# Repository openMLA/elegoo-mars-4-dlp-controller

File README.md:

# Raspberry Pi hat for Elegoo Mars 4 DLP board 

A hat for the raspberry pi that allows a resin 3D printer's **UV light** projector to be controlled. Note that this is (in direct form) only suitable for the projector in the Mars 4 DLP. If you have other boards check out the repository for the [Anycubic Photon Ultra](https://github.com/openMLA/photon-ultra-controller), or get in touch for modifications needed. 

The designs in this repository then allow you to project arbitrary **2560x1440** images with UV light on a surface. The native projected pixel size is **50μm**, making PCB fabrication an interesting application. All you would need is a bit of glue code to convert the Gerber files to a rasterised image and then you could easily use the existing 3D printer frame to expose PCB boards. Since you have all the files and access to the code, you can easily tune it to whatever production needs you have.

The UV projector of the Elegoo Mars 4 DLP is [developed and produced by Anhua (D63ZS50B)](https://www.anhuaoe.com/en/industriause/info.aspx?itemid=2694), and seems to be this variety. Under the hood it uses the Texas Instruments DLP300s or DLP301s digital micromirror array.

> [!NOTE]  
> While PCB fabrication is the most straightforward application for this board, this is actually developed as part of an effort towards an open hardware photolithography system. Check out the [openMLA organisation](https://github.com/openMLA/) for more info.

> If you have a projector using the DLPC1438 that uses the parallel video interface (rather than SPI) then you can check out the [PCB design and implementation for the Anycubic Photon Ultra](https://github.com/openMLA/photon-ultra-controller) projector.

### 🚀 At a glance

Running an SPI clock of ~125MHz it takes:

* ~0.75s to send a full 1440p image to the projector
* ~0.18s to send a 720p image to projector

Arbitrary sections of the display can be updated for even shorter transfer times. Note the maximum framerate (below) and that due to technical reasons the smallest image block that can be sent (in terms of transfer size) is 128x2 pixels. 

The image is stored in a buffer in the FPGA, so you can incrementally build or update an image, if that saves you time or makes your life easier.

The max achievable framerate seems to be about 10Hz (as there are some artefacts if you update faster). This is not a hard limit I suspect, and it may be possible to get closer to the display signal framerate of 60Hz.

### 💡 Sourcing the Projector

The easiest and cheapest way to source the projector is to buy a Elegoo Mars 4 DLP. At the time of writing (2024-02-02) the resin printer can be purchased in the EU for 275 euro (discounted).

Alternatively, the projector can be purchased directly from Anhua; but there may be small differences in the heatsink, LED source and other items. Also expect to pay a premium due to shipping, broker cost etc.

### 📃 Project BOM

The total costs for the project consists of 3 parts:

| Expense Description        | Cost  |
| -------------------------- | ----- |
| Elegoo Mars 4 DLP          | 274   |
| Electronics/PCB            | 52.38 |
| Enclosure/3D printed parts | -     |

_The PCB costs are further broken down [in the BOM in the PCB directory](./PCB/README.md)_

### 🎁 3D printable enclosure

A basic 3D printable enclosure is available in the enclosure directory. 

### 🛠 Disassembly 

Disassembly of the printer is not difficult, but I suggest you take a look at the points below before starting.

1. Make sure the projector is working properly by running the display test functions on the original elegoo board.
2. Raise the Z axis all the way to the top. It will only get in the way otherwise. You can also completely remove it later.
3. Remove the front panel. You will need allen keys and philips head screwdrivers. Carefully disconnect the display ribbon cable. Now you should be able to reach the connectors on the mainboard.
4. Disconnect all the connectors on the elegoo mainboard (the one not on top of the projector unit).
5. Undo the screws holding the bottom section of the printer enclosure in place. Now you carefully try to slide it forward and out of the way of the projector. This can be a bit tricky.
6. [optional] If don't want to use the projector in the original elegoo enclosure, you can remove it from the case with the 4 philips head screws holding it in place.

### 🛠 Assembly 

Assembly of the board is pretty straightforward. For completeness, here are the steps you will need to take.

1. Solder headers onto raspberry pi zero.
2. Assembly the custom PCB
3. Flash Raspberry Pi OS Lite onto an micro SD card. You can use [the raspberry pi imager](https://www.raspberrypi.com/software/) for this. Make sure to configure the wireless connection and ssh access in this step.
4. Attach the custom PCB to the raspberry pi zero header.
5. Plug in the 2 pico-claps connectors that were connected to the original elegoo mainboard
6. Plug in the original elegoo power supply to the barrel jack on the custom PCB.
7. Follow the more detailed [software setup](software-setup.md) to get the Pi up and running. 
8. [optional] if you want to use the projector inside the original enclosure, you can check out the instructions in [the enclosure directory](./enclosure/README.md)

### ✅ Future plans

2. Polish package with proper debug level logging and maybe proper formatted python documentation.
3. Add CRC16 checks. (low priority)

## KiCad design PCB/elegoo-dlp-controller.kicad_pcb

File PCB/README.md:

# PCB design

To control the DMD with a raspberry pi, we need a very simple board that allows us to plug in the original Anhua board's connectors (Molex Pico-clasp). Check out [the schematic 🗺](elegoo-dlp-controller.pdf) for the quickest overview of all functionality.

To make our life a little easier, you can add an (optional) dc-dc converter that also converts the 12V to 5V and uses that to power the raspberry pi. This means you do not need to apply separate 5V power to the raspberry pi, and that the 12V needed for the Anhua board provided by the Elegoo Mars 4's power supply is enough to power everything.

Finally, the board breaks out some extra pins for adding your own extra custom bits. SPI and I2C connections, as well as some spare GPIO pins. This may be useful if you want to have exposure occur based on some sensor readout, or maybe tie UV exposure to a simple button for batch production where you don't want to send commands over SSH.

> [!IMPORTANT]  
> Not every connection has been verified to work. I suspect they are all fine since its not a very complex board or high frequency signals. At least the minimum set of pins required for data/exposure seem to work fine.

### Bill of materials

The costs below are indicative, as shipping cost and price changes may have occurred since writing this document. Check with KiCAD's schematic to see if it all up to date. All listed values are including taxes (21%).

| Description                | Supplier         | Supplier Part Number | Amount | Total Cost | Comment                                      |
| -------------------------- | ---------------- | -------------------- | ------ | ---------- | -------------------------------------------- |
| PCB manufacturing          | Aisler           |                      | 3      | 14         | MOC 3pcs                                     |
| Raspberry Pi Zero 2        | Mouser           | 358-SC0510           | 1      | 17         |                                              |
| Micro SD Card (32GB)       | Kiwi Electronics | TS32GUSDU1           | 1      | 10         | Whatever kind you want would work            |
| Raspberry pi header        | Kiwi Electronics | KW-2639              | 1      | 2          | or any basic, cheaper header                 |
| Raspberry pi header female | Kiwi Electronics | KW-1650              | 1      | 1.5        |                                              |
| JST SH 4-pin               | Mouser           | 474-PRT-14417        | 1      | 0.67       | Optional, allows i2c through  stemmaQT/QWIIC |
| Molex PicoClasp 12 pin     | Mouser           | 538-501331-1207      | 1      | 1.19       |                                              |
| Molex PicoClasp 8 pin      | Mouser           | 538-501331-0807      | 1      | 0.92       |                                              |
| Cui DC-DC converter        | Mouser           | 490-P78E05-1000      | 1      | 3.45       |                                              |
| Barreljack                 | Mouser           | 490-PJ-002B          | 1      | 0.79       |                                              |
| Schottky Diode             | Mouser           | 771-PMEG1020EJ-T/R   | 1      | 0.29       |                                              |
| 100uF capacitor            | Mouser           | 667-EEE-FN1E101UP    | 1      | 0.57       |                                              |
|                            |                  |                      |        |            |                                              |
| Total                      |                  |                      |        | 52.38      |                                              |

### Miscellaneous

* Board was designed in KiCAD 7.0
* I had the board fabricated at Aisler (Germany), at 14 euros (total) for 3 boards.

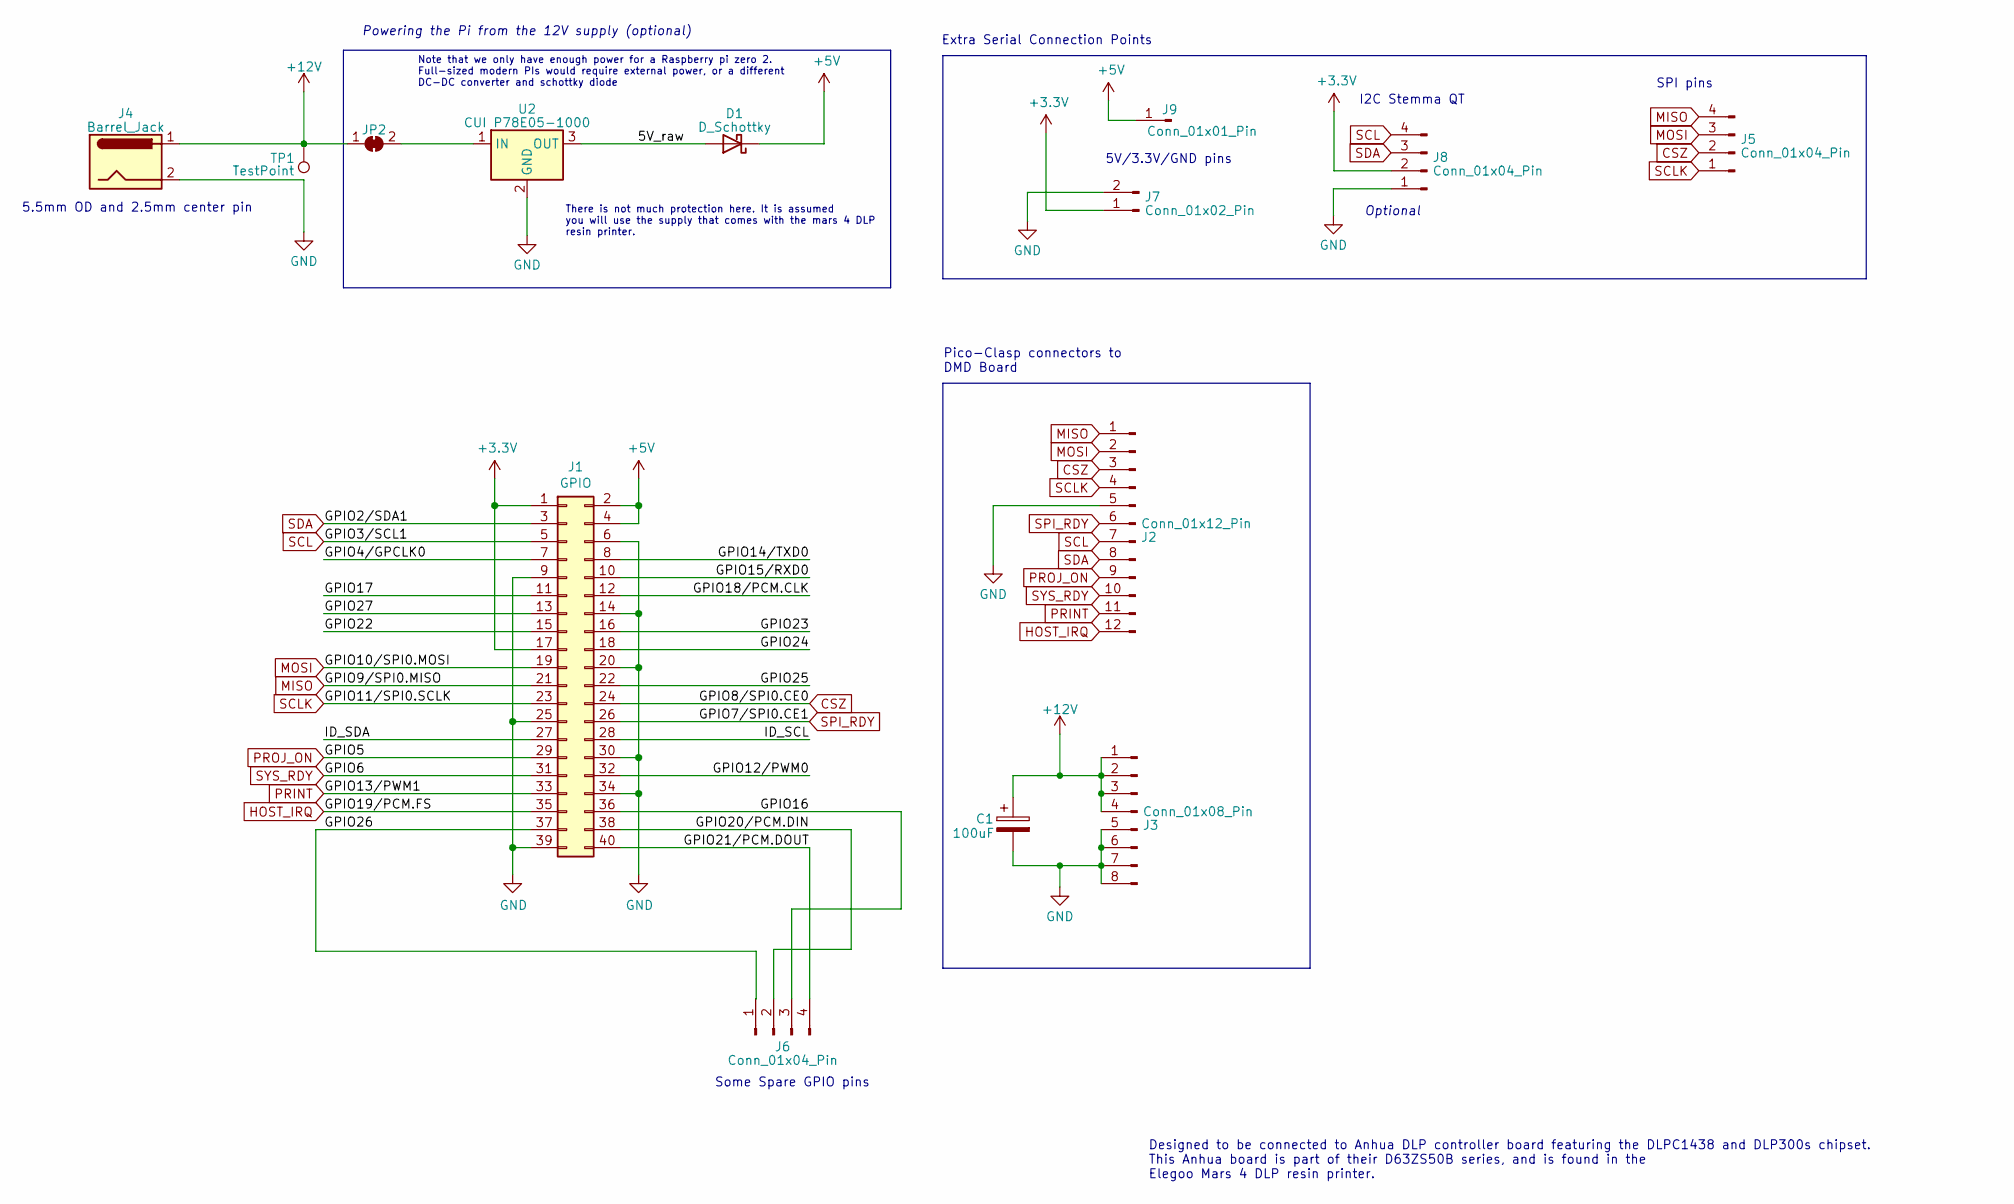
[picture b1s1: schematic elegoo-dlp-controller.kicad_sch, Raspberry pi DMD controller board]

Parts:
C1: 100uF; CP_Elec_6.3x5.8; Mouser 667-EEE-FN1E101UP
D1: D_Schottky; D_SOD-323_HandSoldering; Mouser 771-PMEG1020EJ-T/R
J1: GPIO; PinSocket_2x20_P2.54mm_Vertical
J2: Conn_01x12_Pin; Molex_Pico-Clasp_501331-1207_1x12-1MP_P1.00mm_Vertical; Mouser 538-501331-1207
J3: Conn_01x08_Pin; Molex_Pico-Clasp_501331-0807_1x08-1MP_P1.00mm_Vertical; Mouser 538-501331-0807
J4: Barrel_Jack; BarrelJack_GCT_DCJ200-10-A_Horizontal; Mouser 490-PJ-002B
J5: Conn_01x04_Pin; PinHeader_1x04_P2.54mm_Vertical
J6: Conn_01x04_Pin; PinHeader_2x02_P2.54mm_Vertical
J7: Conn_01x02_Pin; PinHeader_1x02_P2.54mm_Vertical
J8: Conn_01x04_Pin; JST_SH_SM04B-SRSS-TB_1x04-1MP_P1.00mm_Horizontal; Mouser 485-4208
J9: Conn_01x01_Pin; PinHeader_1x01_P2.54mm_Vertical
JP2: SolderJumper_2_Bridged; SolderJumper-2_P1.3mm_Open_TrianglePad1.0x1.5mm
TP1: TestPoint; TestPoint_Pad_D1.5mm
U2: CUI P78E05-1000; Converter_DCDC_RECOM_R-78E-0.5_THT; Mouser 490-P78E05-1000

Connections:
+3V3: J1.1, J1.17, J7.1, J8.2
+5V: D1.1 (K), J1.2, J1.4, J9.1
+12V: C1.1, J3.1, J3.2, J3.3, J3.4, J4.1, JP2.1 (A), TP1.1
/5V_raw: D1.2 (A), U2.3 (OUT)
/GPIO4/GPCLK0: J1.7
/GPIO12/PWM0: J1.32
/GPIO14/TXD0: J1.8
/GPIO15/RXD0: J1.10
/GPIO16: J1.36, J6.3
/GPIO17: J1.11
/GPIO18/PCM.CLK: J1.12
/GPIO20/PCM.DIN: J1.38, J6.2
/GPIO21/PCM.DOUT: J1.40, J6.4
/GPIO22: J1.15
/GPIO23: J1.16
/GPIO24: J1.18
/GPIO25: J1.22
/GPIO26: J1.37, J6.1
/GPIO27: J1.13
/ID_SCL: J1.28
/ID_SDA: J1.27
CSZ: J1.24, J2.3, J5.2
GND: C1.2, J1.6, J1.9, J1.14, J1.20, J1.25, J1.30, J1.34, J1.39, J2.5, J3.5, J3.6, J3.7, J3.8, J4.2, J7.2, J8.1, U2.2 (GND)
HOST_IRQ: J1.35, J2.12
MISO: J1.21, J2.1, J5.4
MOSI: J1.19, J2.2, J5.3
unnamed: JP2.2 (B), U2.1 (IN)
PRINT: J1.33, J2.11
PROJ_ON: J1.29, J2.9
SCL: J1.5, J2.7, J8.4
SCLK: J1.23, J2.4, J5.1
SDA: J1.3, J2.8, J8.3
SPI_RDY: J1.26, J2.6
SYS_RDY: J1.31, J2.10

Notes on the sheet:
There is not much protection here. It is assumed you will use the supply that comes with the mars 4 DLP resin printer.
Optional
Extra Serial Connection Points
Pico-Clasp connectors to DMD Board
5.5mm OD and 2.5mm center pin
5V/3.3V/GND pins
SPI pins
Some Spare GPIO pins
Note that we only have enough power for a Raspberry pi zero 2. Full-sized modern PIs would require external power, or a different DC-DC converter and schottky diode
I2C Stemma QT
Powering the Pi from the 12V supply (optional)
Designed to be connected to Anhua DLP controller board featuring the DLPC1438 and DLP300s chipset. This Anhua board is part of their D63ZS50B series, and is found in the Elegoo Mars 4 DLP resin printer.

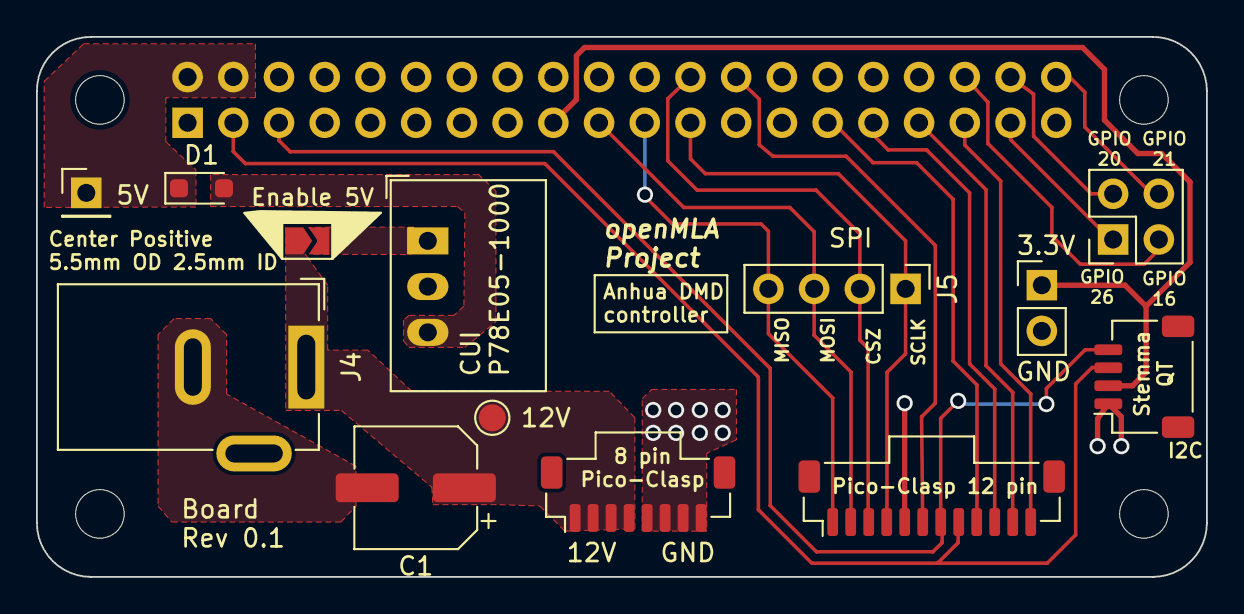
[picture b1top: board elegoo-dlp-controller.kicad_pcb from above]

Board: 2 copper layers, 65.0 x 30.0 mm, 18 parts (1 on the bottom side), 21 nets.

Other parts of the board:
MH1, MH2, MH3, MH4: MountingHole_2.7mm_M2.5

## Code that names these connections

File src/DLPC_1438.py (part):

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from img_convert import image_to_arr

# Pin numbering
PROJ_ON = 5
SYS_RDY = 6
HOST_IRQ = 19
SPI_RDY = 7
PRINT_ACTIVE = 13

SPI_BUFFERSIZE = 65536  # note the default config for raspberry pi is 4096
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def intialise_DLPC1438(i2c_bus):
    """
    Checks if the DCLP1438 is running and ready for i2c communication, and if not, will 
    start the DLPC1438 with the PROJ_ON gpio signal.
    """
    print("Intialising the DLPC1438...")

    # Configure the pins
    GPIO.setup(PROJ_ON, GPIO.OUT)  
    GPIO.setup(SYS_RDY, GPIO.IN)  
    GPIO.setup(HOST_IRQ, GPIO.IN)  
    GPIO.setup(SPI_RDY, GPIO.IN)  
    GPIO.setup(PRINT_ACTIVE, GPIO.IN)  


    ## TODO: avoid this line below, which forces a full restart of the DLPC1438
    # I think it interferes with how the Anhua board is designed...
    GPIO.output(PROJ_ON, GPIO.LOW)    
    time.sleep(1)
        
    # there are 2 options (see figure 9.1 of DLPC1438 datasheet):
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
        # send the PROJ_ON signal and wait for the HOST_IRQ signal to go high, signalling the DLPC1438
        # is ready to go
        GPIO.output(PROJ_ON, GPIO.HIGH)
        ref_time = time.time()
        while not GPIO.input(HOST_IRQ):
            time.sleep(0.01)

        print(f"DLPC1438 is signalling it is ready for use, {time.time()-ref_time} seconds after PROJ_ON went high.")
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

def  await_SYS_RDY():
    while not GPIO.input(SYS_RDY):
        time.sleep(0.3)
        print("waiting for SYS_RDY")


def expose_pattern(exposure_time,i2c_bus):
    assert GPIO.input(SYS_RDY), "SYS_RDY signal is not high yet, cannot expose frames yet."

    # Write External Print Control (C1)
    # start exposure of current buffer for infinite duration with 5 dark frames to let video data stabilise)
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    # the value above never seem to be read back correctly if you read over I2C. Also on anyubic board.'

    time.sleep(0.1)
    if not GPIO.input(PRINT_ACTIVE): warnings.warn("PRINT ACTIVE did not go high after starting exposure. Something might be wrong.") 

    

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    i2c_bus.write_i2c_block_data(DLPC1438_addr, 0xC5, [0x00])  
    time.sleep(0.3)

    if not GPIO.input(SPI_RDY): warnings.warn("FPGA not ready to receive SPI data")  # TODO: check if this pin ever goes high

    # Note that xfer3 has a max number of bytes it can transfer set in /sys/module/spidev/parameters/bufsiz
    spi_bus.xfer3(format_spi_data(3, 4, 400, pxldata))
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    i2c_bus.write_i2c_block_data(DLPC1438_addr, 0x67, [0b00000011, 0x0B]) 
    print(f"FPGA testpattern settings: {[hex(val) for val in i2c_bus.read_i2c_block_data(DLPC1438_addr,0x68,2)]}")

    if not GPIO.input(SPI_RDY): warnings.warn("FPGA not ready to receive SPI data")
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
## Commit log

2024-02-04 Intial commit
2024-02-04 Add licence information
2024-02-04 Add Raspberry Pi uHAT template
2024-02-05 Add initial draft of PCB
2024-02-07 change dc converter and switch to vertical connectors
2024-02-08 Connect SPI_RDY and minor retouching
2024-02-19 Initial basic version of code
    confirms that PCB version 0.1 is able to power the board and that is enables the bootup GPIO signals and I2c
2024-02-21 Refactor startup code
2024-02-21 Add proper checked mode switch function
    Mode switch is now abstracted behind a function with enum input and that checks for succesfull mode switch.
2024-02-21 Add intial external print mode code
    Adds basic configuration options for EXTERNAL PRINT mode, as extracted from the I2C signals from the elegoo board.
2024-02-22 Implement early SPI transmission and minimal exposing code
    Added formatted SPI data transmission code. ALso changed some of the registers around to the point where the code will at least turn the projector mode in external print mode. The SPI data transmissi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
2024-02-25 Working Single-spi-transfer image code
    Added functional code and test image for a setting 256x144px image over a single SPI command.
2024-02-25 Split SPI transfer slow implementation
    A functional, but slow implentation of image transfer over SPI split between different transmissions to get around a finite SPI buffer size.
2024-02-25 Faster SPI transfers
    Rewrite some code in numpy operations and use numpy arrays instead of lists with spidev.writebytes2. In addition increased the (max) SPI clock to 30MHz. Now 720p image takes ~0.5s to transfer.
2024-02-28 Add 3D models to PCB
    Added some step files for the 3D view of the PCB. Will also be useful for the design of the enclosure.
2024-02-28 Add PCB readme and BOM
2024-02-28 Expand READMEs
    Fix some formatting issues. Add more information to the main readme.
2024-03-01 Improve function syntax split spi
    Made the syntax more versatile for the send_split_image_buffer function.
2024-03-02 Move to object-oriented and implement buffer swap, pwm, and exposure time
    Big refactor in moving to object oriented formulation for code. Cleaned up the code a bit with some convenience functions. Made into a more appropriate package form. Implemented the SPI buffer swap f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
2024-03-02 Update main readme
    Clean up current projec status and remove errant line.
2024-03-06 Fix set_background function speed issue
    Fix for issue https://github.com/openMLA/elegoo-mars-4-dlp-controller/issues. The problem was that integer type was incorrect (32 vs 8bit), and cast operations took a while. The 2nd issue was that fo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
2024-03-07 Add 1440p test image
2024-03-07 Fix SPI transfer and refactor functions
    Fixed issue with SPI transfer due to error in TI documentation. Images can now properly be displayed, even when updating only part of the frame. Multiple writes to the same buffer also works. Higher 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
2024-03-07 Remove image inversion
    Img_convert inverted the image, but this was only for testing purposes and has therefore been removed.
2024-03-08 Add enclosure design files
    Add the design files for a basic 3D pritnable enclosure. Update documentation to contain some more information on dissembly of the printer and how to assemble the new unit.
2024-03-08 Add software setup instructions
2024-03-08 Fix markdown syntax error in software-setup
2024-03-08 Fix padding code error
    Fixed issue in padding calculation. In some cases it would produce the incorrect result. Now has the correct logic.
2024-03-08 Add option and example to send array data
    Add option to directly send an array to the DMD, rather than just an image file path. Added example in main.py to show this use.
2024-03-08 Add banner image
    Simple image to show custom projected image
2024-04-13 Add reference to anycubic-photon-ultra project
    Reference other DLPC1438 project.
2025-11-29 Update schematic pdf reflect latest version of kicad project
    The pdf was not kept up to date with the kicad file. Thanks to github user wjsteele for pointing this out. See issue https://github.com/openMLA/elegoo-mars-4-dlp-controller/issues/11
